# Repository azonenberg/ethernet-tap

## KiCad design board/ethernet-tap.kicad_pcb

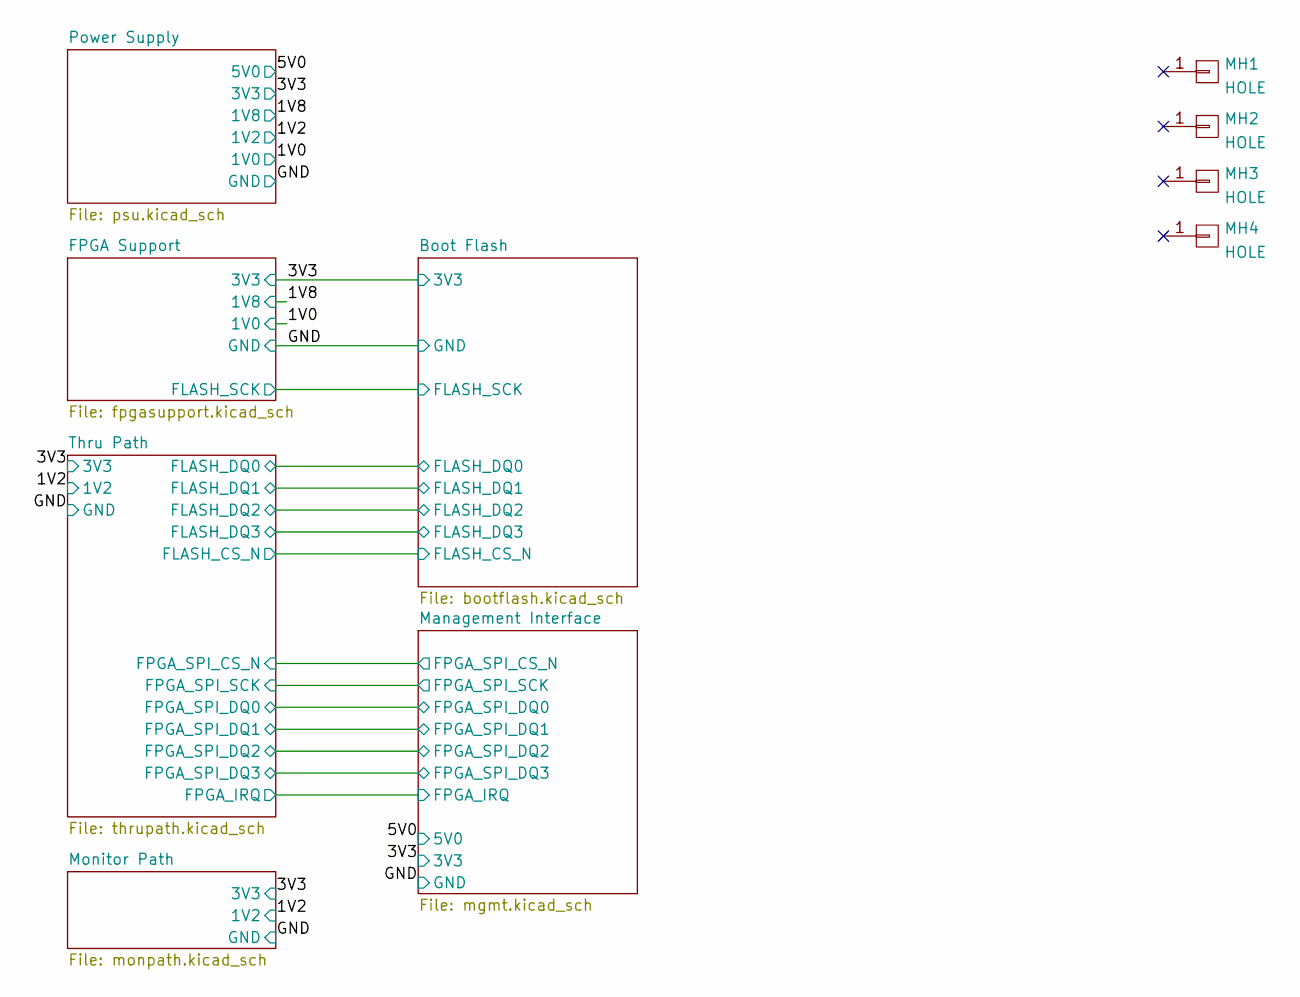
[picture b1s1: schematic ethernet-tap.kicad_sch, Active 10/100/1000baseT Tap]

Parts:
MH1, MH2, MH3, MH4: HOLE; MECHANICAL_CLEARANCEHOLE_4_40

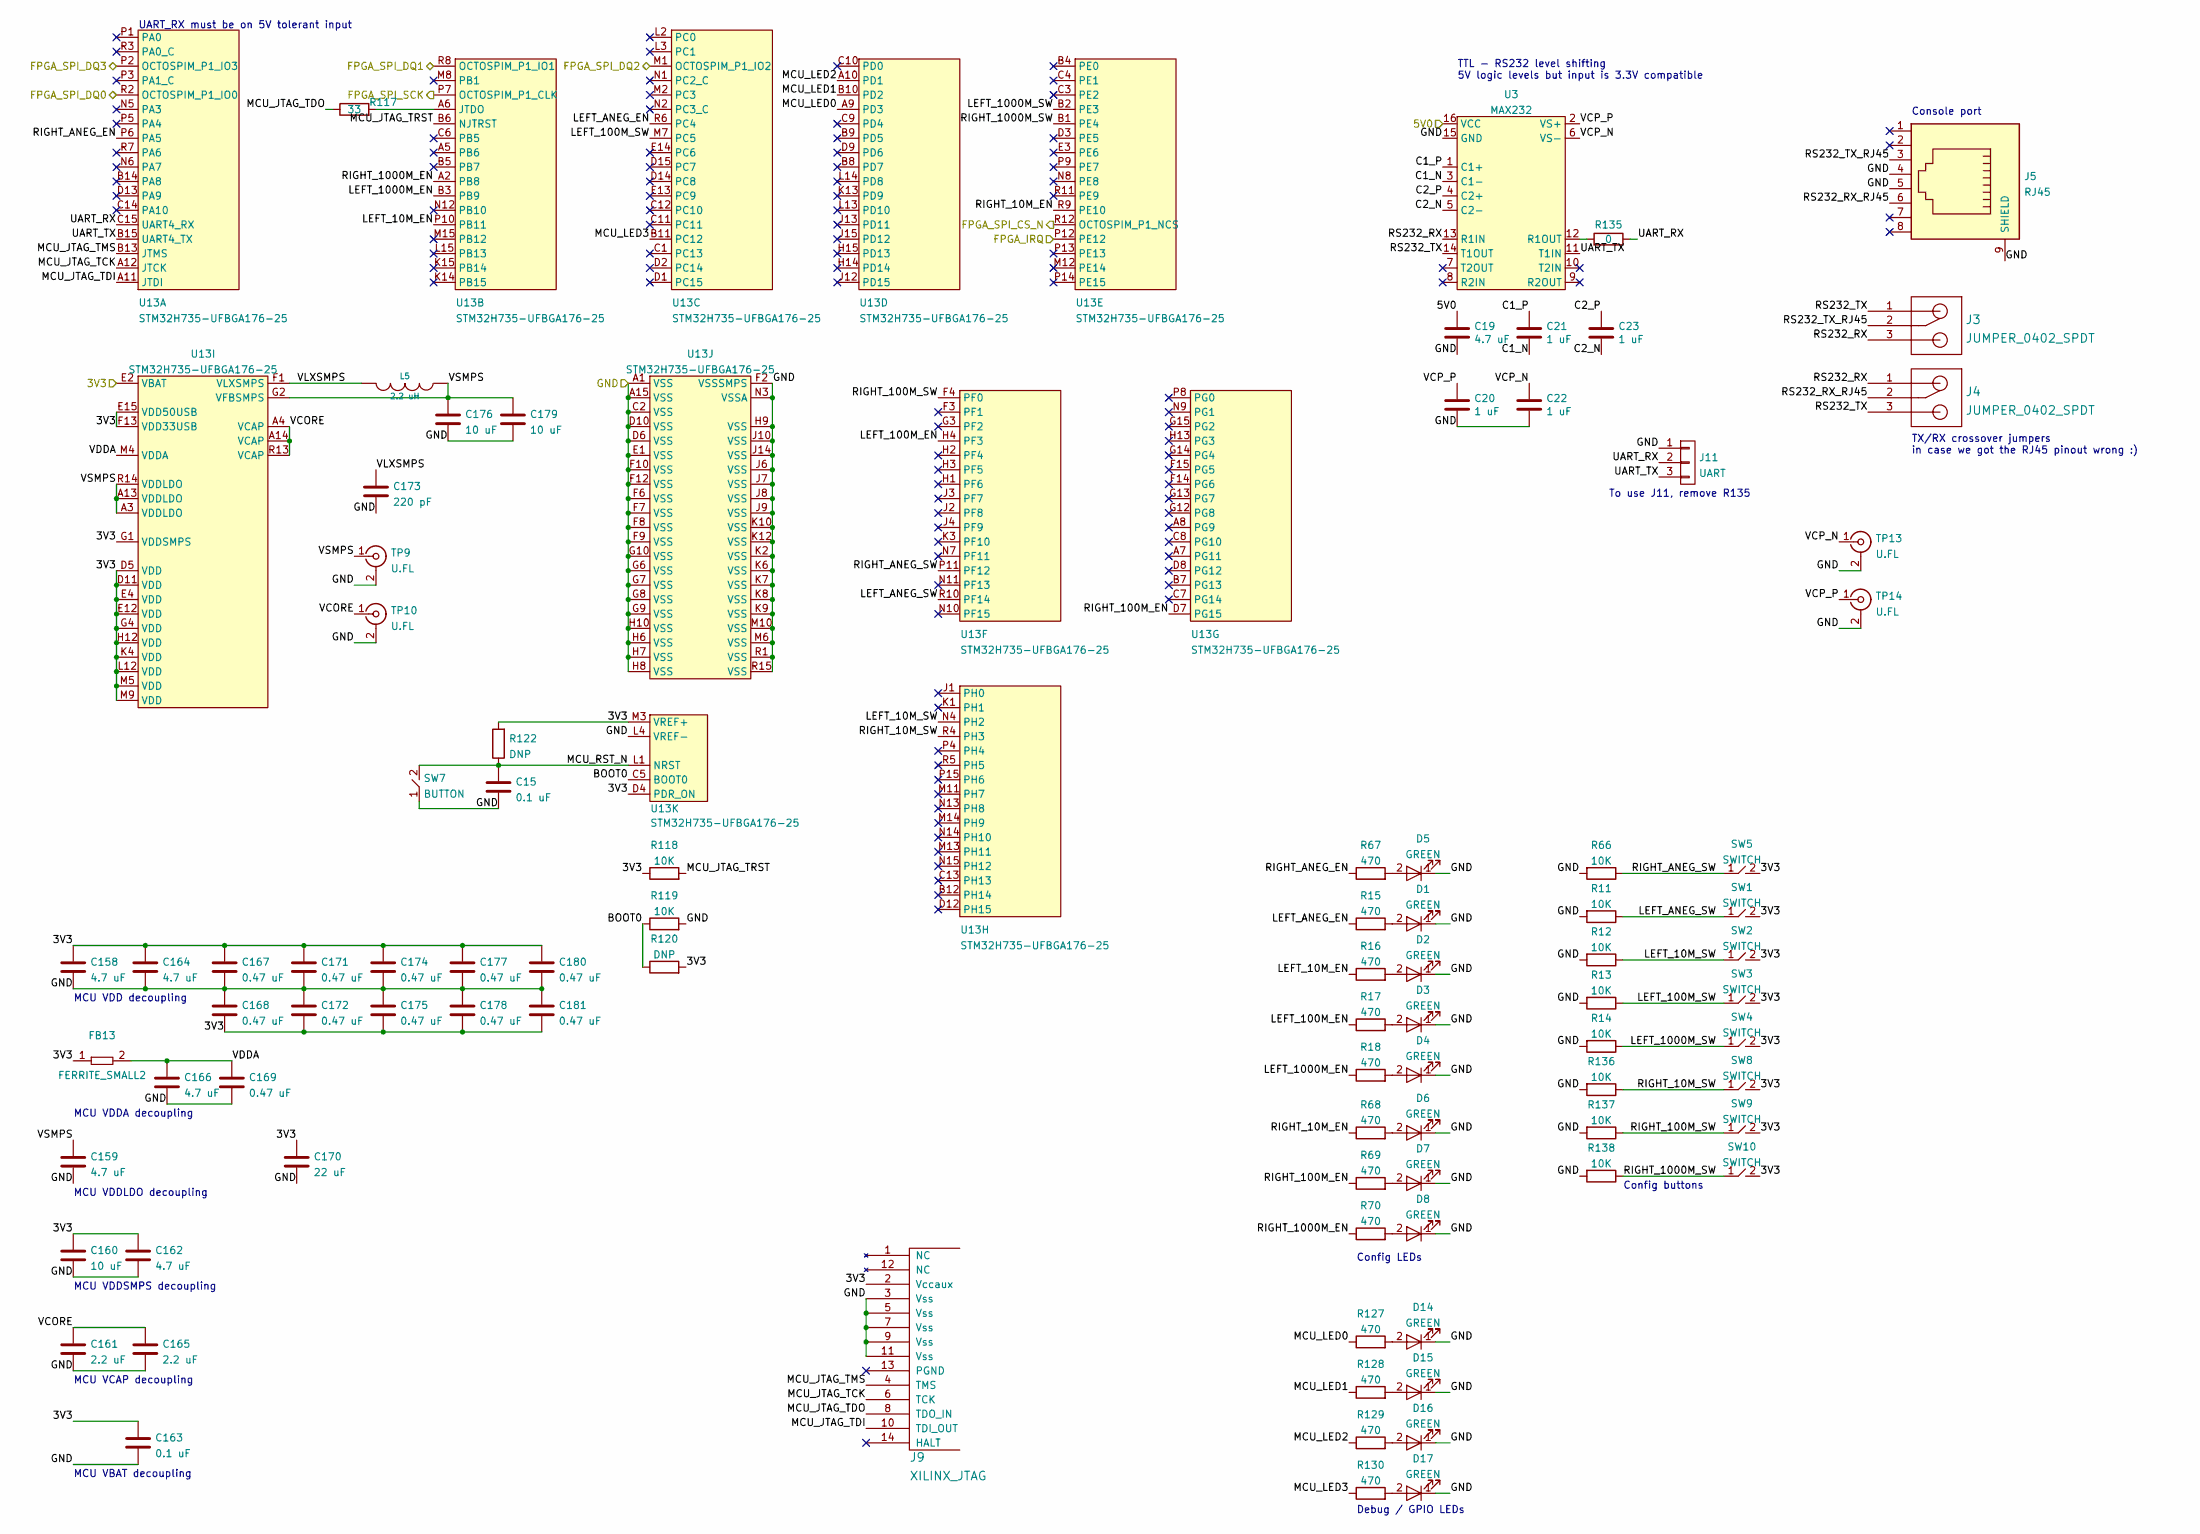
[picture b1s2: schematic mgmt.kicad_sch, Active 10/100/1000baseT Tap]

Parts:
C15, C163: 0.1 uF; EIA_0402_CAP_NOSILK
C19, C158, C159, C162, C164, C166: 4.7 uF; EIA_0603_CAP_NOSILK
C20, C21, C22, C23: 1 uF; EIA_0603_CAP_NOSILK
C160, C176, C179: 10 uF; EIA_0805_CAP_NOSILK
C161, C165: 2.2 uF; EIA_0603_CAP_NOSILK
C167, C168, C169, C171, C172, C174, C175, C177, C178, C180, C181: 0.47 uF; EIA_0402_CAP_NOSILK
C170: 22 uF; EIA_1206_CAP_NOSILK
C173: 220 pF; EIA_0402_CAP_NOSILK
D1, D2, D3, D4, D5, D6, D7, D8, D14, D15, D16, D17: GREEN; EIA_0603_LED
FB13: FERRITE_SMALL2; EIA_0603_INDUCTOR_NOSILK
J3, J4: JUMPER_0402_SPDT; EIA_0402_JUMPER
J5: RJ45; CONN_RJ45_BELSTEWART_SS-7188S-A-PG4-1-BA-xx
J9: XILINX_JTAG; XILINX_JTAG_PTH_MOLEX_0878311420
J11: UART; CONN_HEADER_2.54MM_1x3
L5: 2.2 uH; EIA_1210_CAP_NOSILK
R11, R12, R13, R14, R66, R118, R119, R136, R137, R138: 10K; EIA_0402_RES_NOSILK
R15, R16, R17, R18, R67, R68, R69, R70, R127, R128, R129, R130: 470; EIA_0402_RES_NOSILK
R117: 33; EIA_0402_RES_NOSILK
R120, R122: DNP; EIA_0402_RES_NOSILK
R135: 0; EIA_0402_RES_NOSILK
SW1, SW2, SW3, SW4, SW5, SW8, SW9, SW10: SWITCH; SWITCH_RAFI_MICON_5
SW7: BUTTON; SWITCH_RAFI_MICON_5
TP9, TP10, TP13, TP14: U.FL; CONN_U.FL_TE_1909763-1
U3: MAX232; SOIC_16_3.9MM
U13: STM32H735-UFBGA176-25; BGA_201_10x10_DEPOP_0.65MM_OSHPARK

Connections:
/3V3: C158.1, C160.1, C162.1, C163.1, C164.1, C167.1, C168.2, C170.1, C171.1, C172.2, C174.1, C175.2, C177.1, C178.2, C180.1, C181.2, FB13.1, J9.2 (Vccaux), R118.1, R120.2, R122.2, SW1.2, SW2.2, SW3.2, SW4.2, SW5.2, SW8.2, SW9.2, SW10.2, U13.D4 (PDR_ON), U13.D5 (VDD), U13.D11 (VDD), U13.E2 (VBAT), U13.E4 (VDD), U13.E12 (VDD), U13.E15 (VDD50USB), U13.F13 (VDD33USB), U13.G1 (VDDSMPS), U13.G4 (VDD), U13.H12 (VDD), U13.K4 (VDD), U13.L12 (VDD), U13.M3 (VREF+), U13.M5 (VDD), U13.M9 (VDD); also elsewhere on the board
/5V0: C19.1, U3.16 (VCC); also elsewhere on the board
/GND: C15.2, C19.2, C20.2, C22.2, C158.2, C159.2, C160.2, C161.2, C162.2, C163.2, C164.2, C165.2, C166.2, C167.2, C168.1, C169.2, C170.2, C171.2, C172.1, C173.2, C174.2, C175.1, C176.2, C177.2, C178.1, C179.2, C180.2, C181.1, D1.1 (K), D2.1 (K), D3.1 (K), D4.1 (K), D5.1 (K), D6.1 (K), D7.1 (K), D8.1 (K), D14.1 (K), D15.1 (K), D16.1 (K), D17.1 (K), J5.4, J5.5, J5.9 (SHIELD), J9.3 (Vss), J9.5 (Vss), J9.7 (Vss), J9.9 (Vss), J9.11 (Vss), J11.1, R11.2, R12.2, R13.2, R14.2, R66.2, R119.2, R136.2, R137.2, R138.2, SW7.1, TP9.2 (Ext), TP10.2 (Ext), TP13.2 (Ext), TP14.2 (Ext), U3.15 (GND), U13.A1 (VSS), U13.A15 (VSS), U13.C2 (VSS), U13.D6 (VSS), U13.D10 (VSS), U13.E1 (VSS), U13.F2 (VSSSMPS), U13.F6 (VSS), U13.F7 (VSS), U13.F8 (VSS), U13.F9 (VSS), U13.F10 (VSS), U13.F12 (VSS), U13.G6 (VSS), U13.G7 (VSS), U13.G8 (VSS), U13.G9 (VSS), U13.G10 (VSS), U13.H6 (VSS), U13.H7 (VSS), U13.H8 (VSS), U13.H9 (VSS), U13.H10 (VSS), U13.J6 (VSS), U13.J7 (VSS), U13.J8 (VSS), U13.J9 (VSS), U13.J10 (VSS), U13.J14 (VSS), U13.K2 (VSS), U13.K6 (VSS), U13.K7 (VSS), U13.K8 (VSS), U13.K9 (VSS), U13.K10 (VSS), U13.K12 (VSS), U13.L4 (VREF-), U13.M6 (VSS), U13.M10 (VSS), U13.N3 (VSSA), U13.R1 (VSS), U13.R15 (VSS); also elsewhere on the board
/Management Interface/BOOT0: R119.1, R120.1, U13.C5 (BOOT0)
/Management Interface/C1_N: C21.2, U3.3 (C1-)
/Management Interface/C1_P: C21.1, U3.1 (C1+)
/Management Interface/C2_N: C23.2, U3.5 (C2-)
/Management Interface/C2_P: C23.1, U3.4 (C2+)
/Management Interface/FPGA_IRQ: U13.P12 (PE12); also elsewhere on the board
/Management Interface/FPGA_SPI_CS_N: U13.R12 (OCTOSPIM_P1_NCS); also elsewhere on the board
/Management Interface/FPGA_SPI_DQ0: U13.R2 (OCTOSPIM_P1_IO0); also elsewhere on the board
/Management Interface/FPGA_SPI_DQ1: U13.R8 (OCTOSPIM_P1_IO1); also elsewhere on the board
/Management Interface/FPGA_SPI_DQ2: U13.M1 (OCTOSPIM_P1_IO2); also elsewhere on the board
/Management Interface/FPGA_SPI_DQ3: U13.P2 (OCTOSPIM_P1_IO3); also elsewhere on the board
/Management Interface/FPGA_SPI_SCK: U13.P7 (OCTOSPIM_P1_CLK); also elsewhere on the board
/Management Interface/LEFT_10M_EN: R16.1, U13.P10 (PB11)
/Management Interface/LEFT_10M_SW: R12.1, SW2.1, U13.N4 (PH2)
/Management Interface/LEFT_100M_EN: R17.1, U13.H4 (PF3)
/Management Interface/LEFT_100M_SW: R13.1, SW3.1, U13.M7 (PC5)
/Management Interface/LEFT_1000M_EN: R18.1, U13.B3 (PB9)
/Management Interface/LEFT_1000M_SW: R14.1, SW4.1, U13.B2 (PE3)
/Management Interface/LEFT_ANEG_EN: R15.1, U13.R6 (PC4)
/Management Interface/LEFT_ANEG_SW: R11.1, SW1.1, U13.R10 (PF14)
/Management Interface/MCU_JTAG_TCK: J9.6 (TCK), U13.A12 (JTCK)
/Management Interface/MCU_JTAG_TDI: J9.10 (TDI_OUT), U13.A11 (JTDI)
/Management Interface/MCU_JTAG_TDO: J9.8 (TDO_IN), R117.1
/Management Interface/MCU_JTAG_TMS: J9.4 (TMS), U13.B13 (JTMS)
/Management Interface/MCU_JTAG_TRST: R118.2, U13.B6 (NJTRST)
/Management Interface/MCU_LED0: R127.1, U13.A9 (PD3)
/Management Interface/MCU_LED1: R128.1, U13.B10 (PD2)
/Management Interface/MCU_LED2: R129.1, U13.A10 (PD1)
/Management Interface/MCU_LED3: R130.1, U13.B11 (PC12)
/Management Interface/MCU_RST_N: C15.1, R122.1, SW7.2, U13.L1 (NRST)
/Management Interface/RIGHT_10M_EN: R68.1, U13.R9 (PE10)
/Management Interface/RIGHT_10M_SW: R136.1, SW8.1, U13.R4 (PH3)
/Management Interface/RIGHT_100M_EN: R69.1, U13.D7 (PG15)
/Management Interface/RIGHT_100M_SW: R137.1, SW9.1, U13.F4 (PF0)
/Management Interface/RIGHT_1000M_EN: R70.1, U13.A2 (PB8)
/Management Interface/RIGHT_1000M_SW: R138.1, SW10.1, U13.B1 (PE4)
/Management Interface/RIGHT_ANEG_EN: R67.1, U13.P6 (PA5)
/Management Interface/RIGHT_ANEG_SW: R66.1, SW5.1, U13.P11 (PF12)
/Management Interface/RS232_RX: J3.3, J4.1, U3.13 (R1IN)
/Management Interface/RS232_RX_RJ45: J4.2, J5.6
/Management Interface/RS232_TX: J3.1, J4.3, U3.14 (T1OUT)
/Management Interface/RS232_TX_RJ45: J3.2, J5.3
/Management Interface/UART_RX: J11.2, R135.2, U13.C15 (UART4_RX)
/Management Interface/UART_TX: J11.3, U3.11 (T1IN), U13.B15 (UART4_TX)
/Management Interface/VCORE: C161.1, C165.1, TP10.1 (In), U13.A4 (VCAP), U13.A14 (VCAP), U13.R13 (VCAP)
/Management Interface/VCP_N: C22.1, TP13.1 (In), U3.6 (VS-)
/Management Interface/VCP_P: C20.1, TP14.1 (In), U3.2 (VS+)
/Management Interface/VDDA: C166.1, C169.1, FB13.2, U13.M4 (VDDA)
/Management Interface/VLXSMPS: C173.1, L5.2, U13.F1 (VLXSMPS)
/Management Interface/VSMPS: C159.1, C176.1, C179.1, L5.1, TP9.1 (In), U13.A3 (VDDLDO), U13.A13 (VDDLDO), U13.G2 (VFBSMPS), U13.R14 (VDDLDO)
unnamed: D1.2 (A), R15.2
unnamed: D2.2 (A), R16.2
unnamed: D3.2 (A), R17.2
unnamed: D4.2 (A), R18.2
unnamed: D5.2 (A), R67.2
unnamed: D6.2 (A), R68.2
unnamed: D7.2 (A), R69.2
unnamed: D8.2 (A), R70.2
unnamed: D14.2 (A), R127.2
unnamed: D15.2 (A), R128.2
unnamed: D16.2 (A), R129.2
unnamed: D17.2 (A), R130.2
unnamed: R117.2, U13.A6 (JTDO)
unnamed: R135.1, U3.12 (R1OUT)

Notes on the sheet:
TX/RX crossover jumpers in case we got the RJ45 pinout wrong :)
MCU VCAP decoupling
Config buttons
Console port
UART_RX must be on 5V tolerant input
To use J11, remove R135
MCU VDDSMPS decoupling
MCU VDDA decoupling
MCU VBAT decoupling
MCU VDD decoupling
Debug / GPIO LEDs
Config LEDs
MCU VDDLDO decoupling
TTL - RS232 level shifting 5V logic levels but input is 3.3V compatible

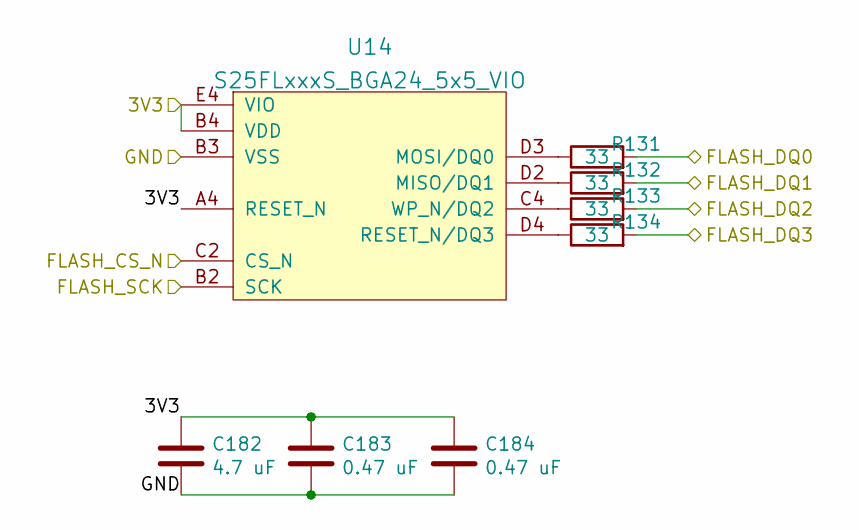
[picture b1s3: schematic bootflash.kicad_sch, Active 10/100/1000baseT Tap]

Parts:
C182: 4.7 uF; EIA_0603_CAP_NOSILK
C183, C184: 0.47 uF; EIA_0402_CAP_NOSILK
R131, R132, R133, R134: 33; EIA_0402_RES_NOSILK
U14: S25FLxxxS_BGA24_5x5_VIO; BGA_24_6x8_DEPOP1_1MM

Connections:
/3V3: C182.1, C183.1, C184.1, U14.A4 (RESET_N), U14.B4 (VDD), U14.E4 (VIO); also elsewhere on the board
/Boot Flash/FLASH_CS_N: U14.C2 (CS_N); also elsewhere on the board
/Boot Flash/FLASH_DQ0: R131.2; also elsewhere on the board
/Boot Flash/FLASH_DQ1: R132.2; also elsewhere on the board
/Boot Flash/FLASH_DQ2: R133.2; also elsewhere on the board
/Boot Flash/FLASH_DQ3: R134.2; also elsewhere on the board
/Boot Flash/FLASH_SCK: U14.B2 (SCK); also elsewhere on the board
/GND: C182.2, C183.2, C184.2, U14.B3 (VSS); also elsewhere on the board
unnamed: R131.1, U14.D3 (MOSI/DQ0)
unnamed: R132.1, U14.D2 (MISO/DQ1)
unnamed: R133.1, U14.C4 (WP_N/DQ2)
unnamed: R134.1, U14.D4 (RESET_N/DQ3)

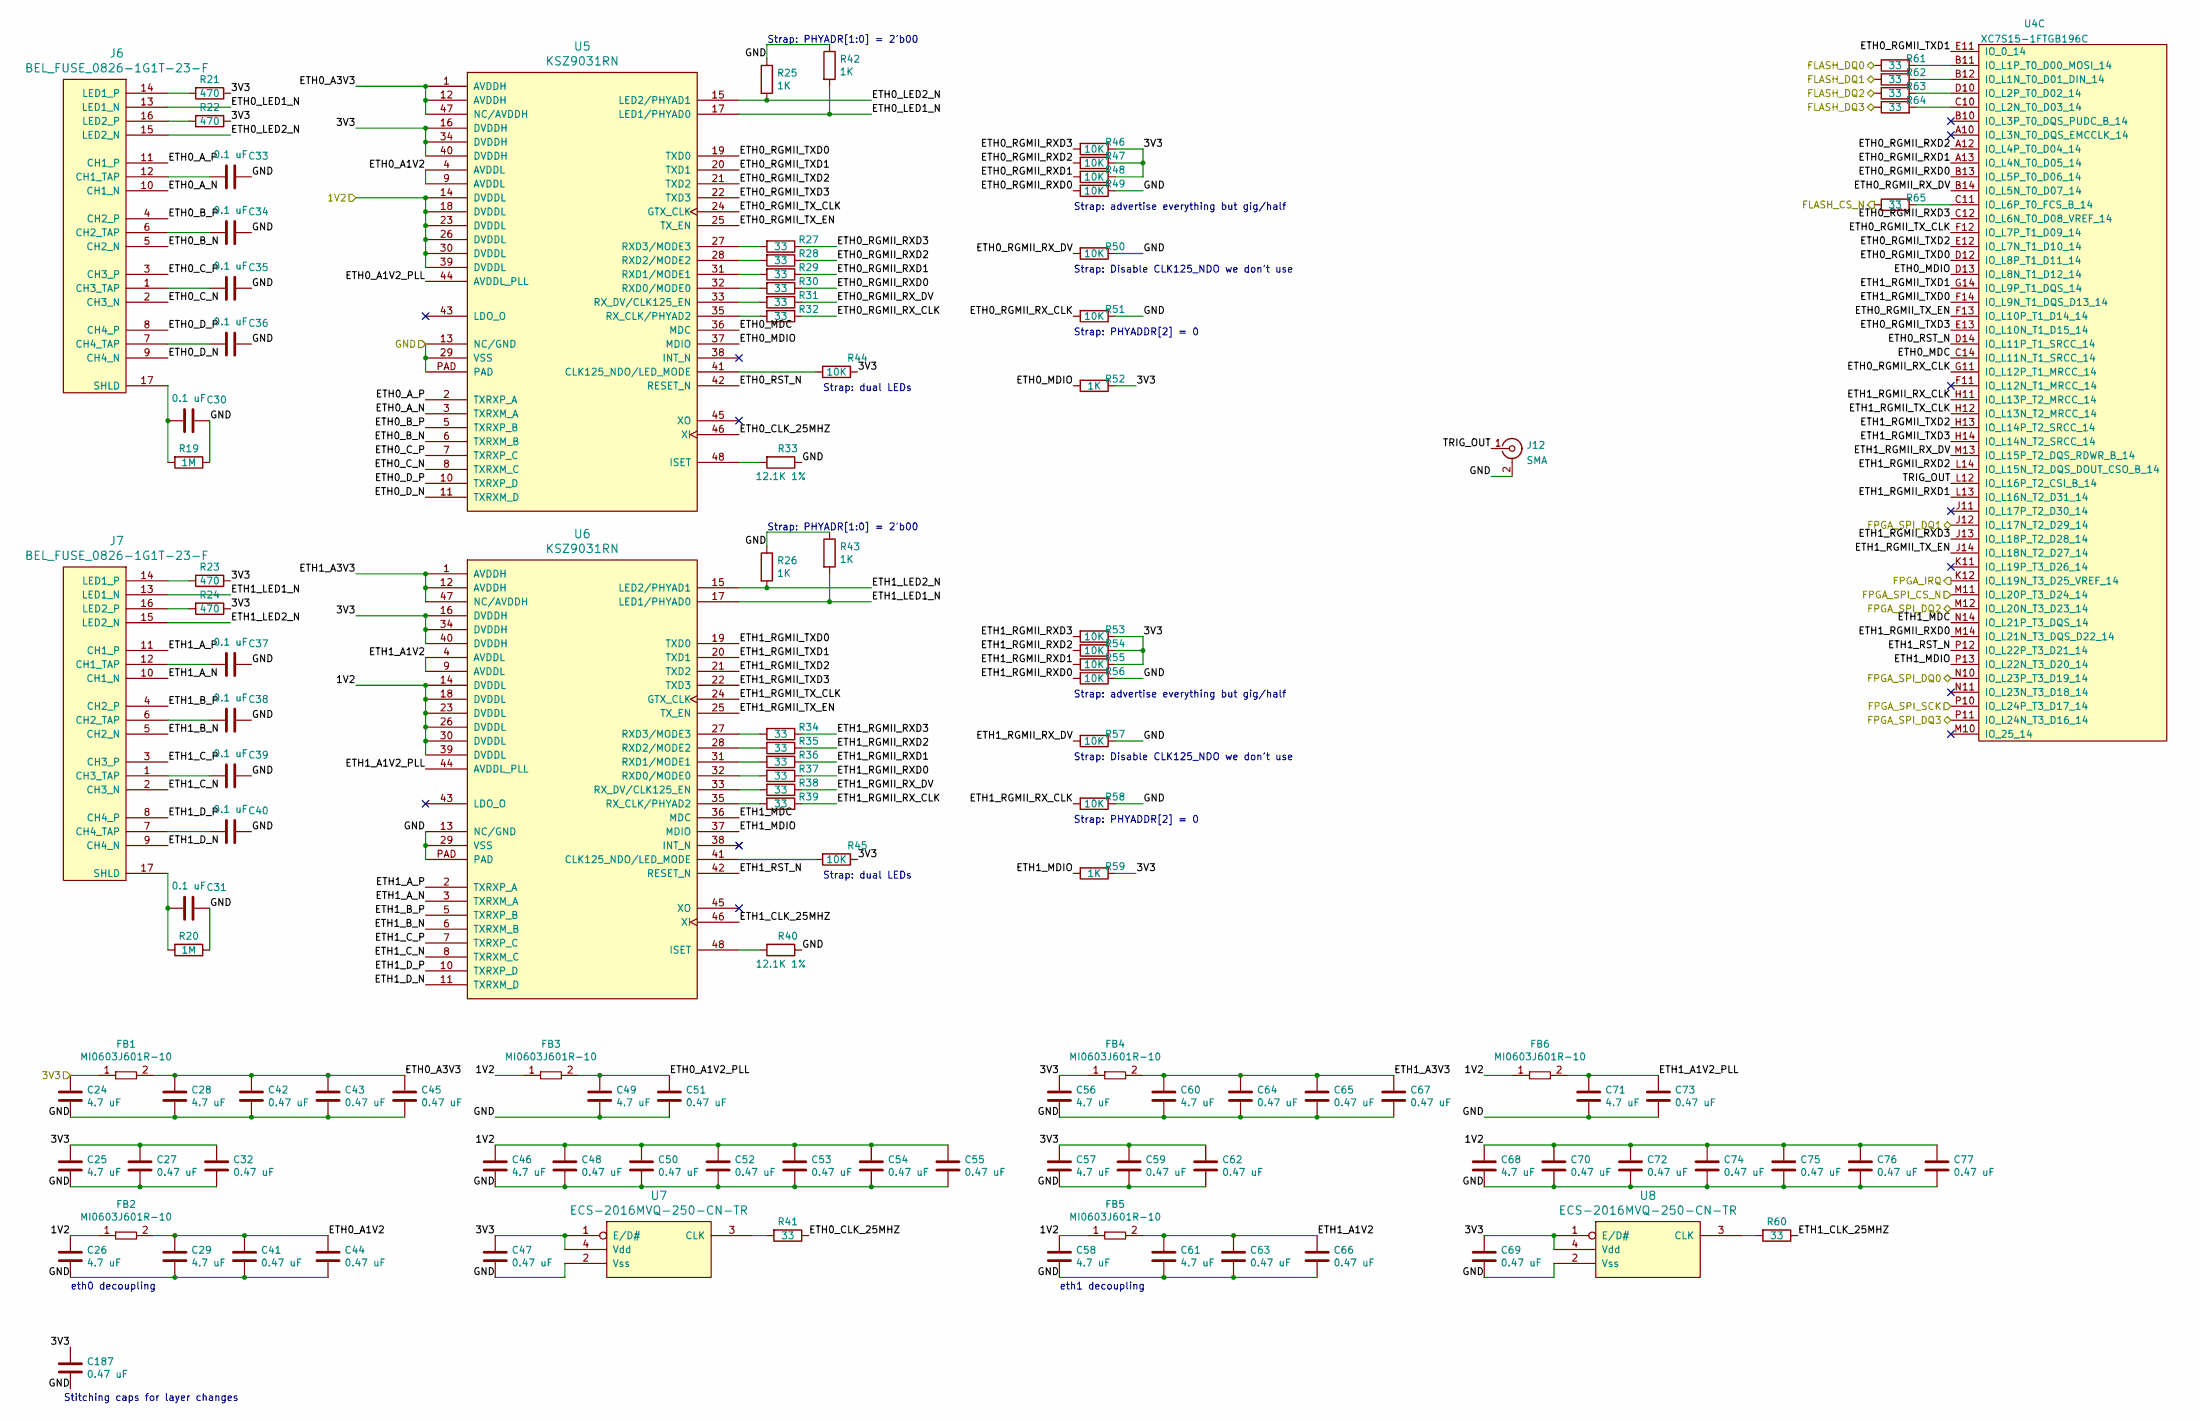
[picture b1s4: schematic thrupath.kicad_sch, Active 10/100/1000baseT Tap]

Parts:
C24, C25, C26, C28, C29, C46, C49, C56, C57, C58, C60, C61, C68, C71: 4.7 uF; EIA_0603_CAP_NOSILK
C27, C32, C41, C42, C43, C44, C45, C47, C48, C50, C51, C52, C53, C54, C55, C59, C62, C63, C64, C65, C66, C67, C69, C70, C72, C73, C74, C75, C76, C77, C187: 0.47 uF; EIA_0402_CAP_NOSILK
C30, C31, C33, C34, C35, C36, C37, C38, C39, C40: 0.1 uF; EIA_0402_CAP_NOSILK
FB1, FB2, FB3, FB4, FB5, FB6: MI0603J601R-10; EIA_0603_INDUCTOR_NOSILK
J6, J7: BEL_FUSE_0826-1G1T-23-F; CONN_BELFUSE_0826_1G1T_23_F
J12: SMA; CONN_SMA_EDGE_SAMTEC_SMA_J_P_H_ST_EM1
R19, R20: 1M; EIA_0402_RES_NOSILK
R21, R22, R23, R24: 470; EIA_0402_RES_NOSILK
R25, R26, R42, R43, R52, R59: 1K; EIA_0402_RES_NOSILK
R27, R28, R29, R30, R31, R32, R34, R35, R36, R37, R38, R39, R41, R60, R61, R62, R63, R64, R65: 33; EIA_0402_RES_NOSILK
R33, R40: 12.1K 1%; EIA_0402_RES_NOSILK
R44, R45, R46, R47, R48, R49, R50, R51, R53, R54, R55, R56, R57, R58: 10K; EIA_0402_RES_NOSILK
U4: XC7S15-1FTGB196C; BGA_196_15x15_FULLARRAY_1MM_FTGB196
U5, U6: KSZ9031RN; QFN_48_0.5MM_7x7MM
U7, U8: ECS-2016MVQ-250-CN-TR; OSCILLATOR_2.0x1.6

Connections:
/1V2: C26.1, C46.1, C48.1, C50.1, C52.1, C53.1, C54.1, C55.1, C58.1, C68.1, C70.1, C72.1, C74.1, C75.1, C76.1, C77.1, FB2.1, FB3.1, FB5.1, FB6.1, U5.14 (DVDDL), U5.18 (DVDDL), U5.23 (DVDDL), U5.26 (DVDDL), U5.30 (DVDDL), U5.39 (DVDDL), U6.14 (DVDDL), U6.18 (DVDDL), U6.23 (DVDDL), U6.26 (DVDDL), U6.30 (DVDDL), U6.39 (DVDDL); also elsewhere on the board
/3V3: C24.1, C25.1, C27.1, C32.1, C47.1, C56.1, C57.1, C59.1, C62.1, C69.1, C187.1, FB1.1, FB4.1, R21.1, R22.1, R23.1, R24.1, R44.1, R45.1, R46.1, R47.1, R48.1, R52.1, R53.1, R54.1, R55.1, R59.1, U5.16 (DVDDH), U5.34 (DVDDH), U5.40 (DVDDH), U6.16 (DVDDH), U6.34 (DVDDH), U6.40 (DVDDH), U7.1 (E/D#), U7.4 (Vdd), U8.1 (E/D#), U8.4 (Vdd); also elsewhere on the board
/Boot Flash/FLASH_CS_N: R65.1; also elsewhere on the board
/Boot Flash/FLASH_DQ0: R61.1; also elsewhere on the board
/Boot Flash/FLASH_DQ1: R62.1; also elsewhere on the board
/Boot Flash/FLASH_DQ2: R63.1; also elsewhere on the board
/Boot Flash/FLASH_DQ3: R64.1; also elsewhere on the board
/GND: C24.2, C25.2, C26.2, C27.2, C28.2, C29.2, C30.1, C31.1, C32.2, C33.1, C34.1, C35.1, C36.1, C37.1, C38.1, C39.1, C40.1, C41.2, C42.2, C43.2, C44.2, C45.2, C46.2, C47.2, C48.2, C49.2, C50.2, C51.2, C52.2, C53.2, C54.2, C55.2, C56.2, C57.2, C58.2, C59.2, C60.2, C61.2, C62.2, C63.2, C64.2, C65.2, C66.2, C67.2, C68.2, C69.2, C70.2, C71.2, C72.2, C73.2, C74.2, C75.2, C76.2, C77.2, C187.2, J12.2 (Ext), R19.1, R20.1, R25.1, R26.1, R33.1, R40.1, R42.1, R43.1, R49.1, R50.1, R51.1, R56.1, R57.1, R58.1, U5.13 (NC/GND), U5.29 (VSS), U5.PAD, U6.13 (NC/GND), U6.29 (VSS), U6.PAD, U7.2 (Vss), U8.2 (Vss); also elsewhere on the board
/Management Interface/FPGA_IRQ: U4.K12 (IO_L19N_T3_D25_VREF_14); also elsewhere on the board
/Management Interface/FPGA_SPI_CS_N: U4.M11 (IO_L20P_T3_D24_14); also elsewhere on the board
/Management Interface/FPGA_SPI_DQ0: U4.N10 (IO_L23P_T3_D19_14); also elsewhere on the board
/Management Interface/FPGA_SPI_DQ1: U4.J12 (IO_L17N_T2_D29_14); also elsewhere on the board
/Management Interface/FPGA_SPI_DQ2: U4.M12 (IO_L20N_T3_D23_14); also elsewhere on the board
/Management Interface/FPGA_SPI_DQ3: U4.P11 (IO_L24N_T3_D16_14); also elsewhere on the board
/Management Interface/FPGA_SPI_SCK: U4.P10 (IO_L24P_T3_D17_14); also elsewhere on the board
/Thru Path/ETH0_A1V2: C29.1, C41.1, C44.1, FB2.2, U5.4 (AVDDL), U5.9 (AVDDL)
/Thru Path/ETH0_A1V2_PLL: C49.1, C51.1, FB3.2, U5.44 (AVDDL_PLL)
/Thru Path/ETH0_A3V3: C28.1, C42.1, C43.1, C45.1, FB1.2, U5.1 (AVDDH), U5.12 (AVDDH), U5.47 (NC/AVDDH)
/Thru Path/ETH0_A_N: J6.10 (CH1_N), U5.3 (TXRXM_A)
/Thru Path/ETH0_A_P: J6.11 (CH1_P), U5.2 (TXRXP_A)
/Thru Path/ETH0_B_N: J6.5 (CH2_N), U5.6 (TXRXM_B)
/Thru Path/ETH0_B_P: J6.4 (CH2_P), U5.5 (TXRXP_B)
/Thru Path/ETH0_CLK_25MHZ: R41.1, U5.46 (XI)
/Thru Path/ETH0_C_N: J6.2 (CH3_N), U5.8 (TXRXM_C)
/Thru Path/ETH0_C_P: J6.3 (CH3_P), U5.7 (TXRXP_C)
/Thru Path/ETH0_D_N: J6.9 (CH4_N), U5.11 (TXRXM_D)
/Thru Path/ETH0_D_P: J6.8 (CH4_P), U5.10 (TXRXP_D)
/Thru Path/ETH0_LED1_N: J6.13 (LED1_N), R42.2, U5.17 (LED1/PHYAD0)
/Thru Path/ETH0_LED2_N: J6.15 (LED2_N), R25.2, U5.15 (LED2/PHYAD1)
/Thru Path/ETH0_MDC: U4.C14 (IO_L11N_T1_SRCC_14), U5.36 (MDC)
/Thru Path/ETH0_MDIO: R52.2, U4.D13 (IO_L8N_T1_D12_14), U5.37 (MDIO)
/Thru Path/ETH0_RGMII_RXD0: R30.1, R49.2, U4.B13 (IO_L5P_T0_D06_14)
/Thru Path/ETH0_RGMII_RXD1: R29.1, R48.2, U4.A13 (IO_L4N_T0_D05_14)
/Thru Path/ETH0_RGMII_RXD2: R28.1, R47.2, U4.A12 (IO_L4P_T0_D04_14)
/Thru Path/ETH0_RGMII_RXD3: R27.1, R46.2, U4.C12 (IO_L6N_T0_D08_VREF_14)
/Thru Path/ETH0_RGMII_RX_CLK: R32.1, R51.2, U4.G11 (IO_L12P_T1_MRCC_14)
/Thru Path/ETH0_RGMII_RX_DV: R31.1, R50.2, U4.B14 (IO_L5N_T0_D07_14)
/Thru Path/ETH0_RGMII_TXD0: U4.D12 (IO_L8P_T1_D11_14), U5.19 (TXD0)
/Thru Path/ETH0_RGMII_TXD1: U4.E11 (IO_0_14), U5.20 (TXD1)
/Thru Path/ETH0_RGMII_TXD2: U4.E12 (IO_L7N_T1_D10_14), U5.21 (TXD2)
/Thru Path/ETH0_RGMII_TXD3: U4.E13 (IO_L10N_T1_D15_14), U5.22 (TXD3)
/Thru Path/ETH0_RGMII_TX_CLK: U4.F12 (IO_L7P_T1_D09_14), U5.24 (GTX_CLK)
/Thru Path/ETH0_RGMII_TX_EN: U4.F13 (IO_L10P_T1_D14_14), U5.25 (TX_EN)
/Thru Path/ETH0_RST_N: U4.D14 (IO_L11P_T1_SRCC_14), U5.42 (RESET_N)
/Thru Path/ETH1_A1V2: C61.1, C63.1, C66.1, FB5.2, U6.4 (AVDDL), U6.9 (AVDDL)
/Thru Path/ETH1_A1V2_PLL: C71.1, C73.1, FB6.2, U6.44 (AVDDL_PLL)
/Thru Path/ETH1_A3V3: C60.1, C64.1, C65.1, C67.1, FB4.2, U6.1 (AVDDH), U6.12 (AVDDH), U6.47 (NC/AVDDH)
/Thru Path/ETH1_A_N: J7.10 (CH1_N), U6.3 (TXRXM_A)
/Thru Path/ETH1_A_P: J7.11 (CH1_P), U6.2 (TXRXP_A)
/Thru Path/ETH1_B_N: J7.5 (CH2_N), U6.6 (TXRXM_B)
/Thru Path/ETH1_B_P: J7.4 (CH2_P), U6.5 (TXRXP_B)
/Thru Path/ETH1_CLK_25MHZ: R60.1, U6.46 (XI)
/Thru Path/ETH1_C_N: J7.2 (CH3_N), U6.8 (TXRXM_C)
/Thru Path/ETH1_C_P: J7.3 (CH3_P), U6.7 (TXRXP_C)
/Thru Path/ETH1_D_N: J7.9 (CH4_N), U6.11 (TXRXM_D)
/Thru Path/ETH1_D_P: J7.8 (CH4_P), U6.10 (TXRXP_D)
/Thru Path/ETH1_LED1_N: J7.13 (LED1_N), R43.2, U6.17 (LED1/PHYAD0)
/Thru Path/ETH1_LED2_N: J7.15 (LED2_N), R26.2, U6.15 (LED2/PHYAD1)
/Thru Path/ETH1_MDC: U4.N14 (IO_L21P_T3_DQS_14), U6.36 (MDC)
/Thru Path/ETH1_MDIO: R59.2, U4.P13 (IO_L22N_T3_D20_14), U6.37 (MDIO)
/Thru Path/ETH1_RGMII_RXD0: R37.1, R56.2, U4.M14 (IO_L21N_T3_DQS_D22_14)
/Thru Path/ETH1_RGMII_RXD1: R36.1, R55.2, U4.L13 (IO_L16N_T2_D31_14)
/Thru Path/ETH1_RGMII_RXD2: R35.1, R54.2, U4.L14 (IO_L15N_T2_DQS_DOUT_CSO_B_14)
/Thru Path/ETH1_RGMII_RXD3: R34.1, R53.2, U4.J13 (IO_L18P_T2_D28_14)
/Thru Path/ETH1_RGMII_RX_CLK: R39.1, R58.2, U4.H11 (IO_L13P_T2_MRCC_14)
/Thru Path/ETH1_RGMII_RX_DV: R38.1, R57.2, U4.M13 (IO_L15P_T2_DQS_RDWR_B_14)
/Thru Path/ETH1_RGMII_TXD0: U4.F14 (IO_L9N_T1_DQS_D13_14), U6.19 (TXD0)
/Thru Path/ETH1_RGMII_TXD1: U4.G14 (IO_L9P_T1_DQS_14), U6.20 (TXD1)
/Thru Path/ETH1_RGMII_TXD2: U4.H13 (IO_L14P_T2_SRCC_14), U6.21 (TXD2)
/Thru Path/ETH1_RGMII_TXD3: U4.H14 (IO_L14N_T2_SRCC_14), U6.22 (TXD3)
/Thru Path/ETH1_RGMII_TX_CLK: U4.H12 (IO_L13N_T2_MRCC_14), U6.24 (GTX_CLK)
/Thru Path/ETH1_RGMII_TX_EN: U4.J14 (IO_L18N_T2_D27_14), U6.25 (TX_EN)
/Thru Path/ETH1_RST_N: U4.P12 (IO_L22P_T3_D21_14), U6.42 (RESET_N)
/Thru Path/TRIG_OUT: J12.1 (In), U4.L12 (IO_L16P_T2_CSI_B_14)
unnamed: C30.2, J6.17 (SHLD), R19.2
unnamed: C31.2, J7.17 (SHLD), R20.2
unnamed: C33.2, J6.12 (CH1_TAP)
unnamed: C34.2, J6.6 (CH2_TAP)
unnamed: C35.2, J6.1 (CH3_TAP)
unnamed: C36.2, J6.7 (CH4_TAP)
unnamed: C37.2, J7.12 (CH1_TAP)
unnamed: C38.2, J7.6 (CH2_TAP)
unnamed: C39.2, J7.1 (CH3_TAP)
unnamed: C40.2, J7.7 (CH4_TAP)
unnamed: J6.14 (LED1_P), R21.2
unnamed: J6.16 (LED2_P), R22.2
unnamed: J7.14 (LED1_P), R23.2
unnamed: J7.16 (LED2_P), R24.2
unnamed: R27.2, U5.27 (RXD3/MODE3)
unnamed: R28.2, U5.28 (RXD2/MODE2)
unnamed: R29.2, U5.31 (RXD1/MODE1)
unnamed: R30.2, U5.32 (RXD0/MODE0)
unnamed: R31.2, U5.33 (RX_DV/CLK125_EN)
unnamed: R32.2, U5.35 (RX_CLK/PHYAD2)
unnamed: R33.2, U5.48 (ISET)
unnamed: R34.2, U6.27 (RXD3/MODE3)
unnamed: R35.2, U6.28 (RXD2/MODE2)
unnamed: R36.2, U6.31 (RXD1/MODE1)
unnamed: R37.2, U6.32 (RXD0/MODE0)
unnamed: R38.2, U6.33 (RX_DV/CLK125_EN)
unnamed: R39.2, U6.35 (RX_CLK/PHYAD2)
unnamed: R40.2, U6.48 (ISET)
unnamed: R41.2, U7.3 (CLK)
unnamed: R44.2, U5.41 (CLK125_NDO/LED_MODE)
unnamed: R45.2, U6.41 (CLK125_NDO/LED_MODE)
unnamed: R60.2, U8.3 (CLK)
unnamed: R61.2, U4.B11 (IO_L1P_T0_D00_MOSI_14)
unnamed: R62.2, U4.B12 (IO_L1N_T0_D01_DIN_14)
unnamed: R63.2, U4.D10 (IO_L2P_T0_D02_14)
unnamed: R64.2, U4.C10 (IO_L2N_T0_D03_14)
unnamed: R65.2, U4.C11 (IO_L6P_T0_FCS_B_14)

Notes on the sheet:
Strap: advertise everything but gig/half
Strap: dual LEDs
Stitching caps for layer changes
Strap: PHYADDR[2] = 0
eth1 decoupling
Strap: PHYADR[1:0] = 2'b00
Strap: Disable CLK125_NDO we don't use
eth0 decoupling

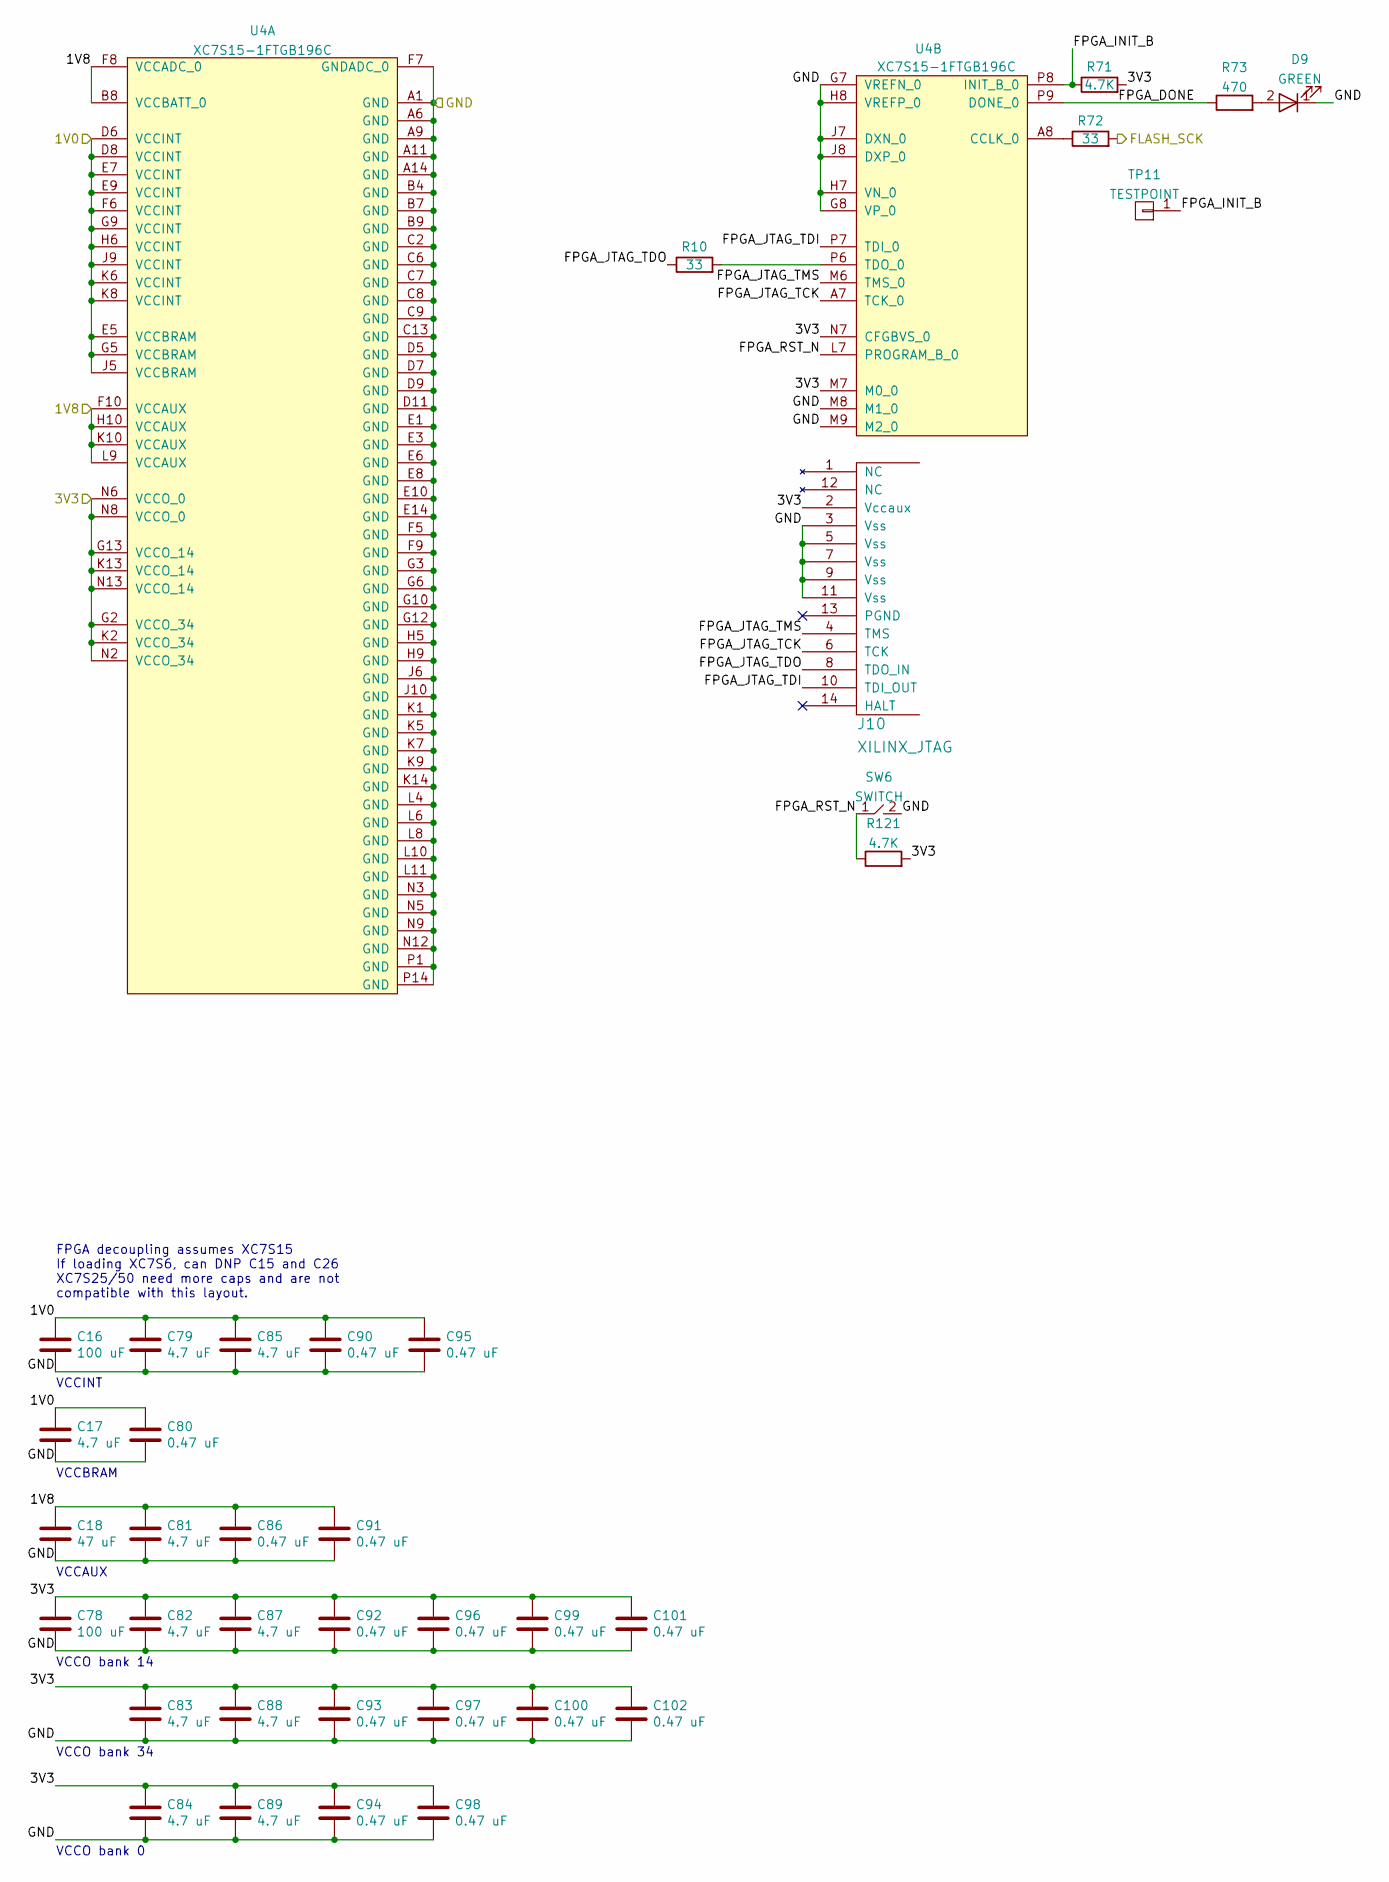
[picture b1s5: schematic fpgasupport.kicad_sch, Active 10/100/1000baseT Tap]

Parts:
C16: 100 uF; EIA_1210_CAP_NOSILK
C17, C79, C81, C82, C83, C84, C85, C87, C88, C89: 4.7 uF; EIA_0603_CAP_NOSILK
C18: 47 uF; EIA_1206_CAP_NOSILK
C78: 100 uF; EIA_1206_CAP_NOSILK
C80, C86, C90, C91, C92, C93, C94, C95, C96, C97, C98, C99, C100, C101, C102: 0.47 uF; EIA_0402_CAP_NOSILK
D9: GREEN; EIA_0603_LED
J10: XILINX_JTAG; XILINX_JTAG_PTH_MOLEX_0878311420
R10, R72: 33; EIA_0402_RES_NOSILK
R71, R121: 4.7K; EIA_0402_RES_NOSILK
R73: 470; EIA_0402_RES_NOSILK
SW6: SWITCH; SWITCH_RAFI_MICON_5
TP11: TESTPOINT; TESTPOINT_SMT_0.5MM
U4: XC7S15-1FTGB196C; BGA_196_15x15_FULLARRAY_1MM_FTGB196

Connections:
/1V0: C16.1, C17.1, C79.1, C80.1, C85.1, C90.1, C95.1, U4.D6 (VCCINT), U4.D8 (VCCINT), U4.E5 (VCCBRAM), U4.E7 (VCCINT), U4.E9 (VCCINT), U4.F6 (VCCINT), U4.G5 (VCCBRAM), U4.G9 (VCCINT), U4.H6 (VCCINT), U4.J5 (VCCBRAM), U4.J9 (VCCINT), U4.K6 (VCCINT), U4.K8 (VCCINT); also elsewhere on the board
/1V8: C18.1, C81.1, C86.1, C91.1, U4.B8 (VCCBATT_0), U4.F8 (VCCADC_0), U4.F10 (VCCAUX), U4.H10 (VCCAUX), U4.K10 (VCCAUX), U4.L9 (VCCAUX); also elsewhere on the board
/3V3: C78.1, C82.1, C83.1, C84.1, C87.1, C88.1, C89.1, C92.1, C93.1, C94.1, C96.1, C97.1, C98.1, C99.1, C100.1, C101.1, C102.1, J10.2 (Vccaux), R71.2, R121.2, U4.G2 (VCCO_34), U4.G13 (VCCO_14), U4.K2 (VCCO_34), U4.K13 (VCCO_14), U4.M7 (M0_0), U4.N2 (VCCO_34), U4.N6 (VCCO_0), U4.N7 (CFGBVS_0), U4.N8 (VCCO_0), U4.N13 (VCCO_14); also elsewhere on the board
/Boot Flash/FLASH_SCK: R72.2; also elsewhere on the board
/FPGA Support/FPGA_DONE: R73.1, U4.P9 (DONE_0)
/FPGA Support/FPGA_INIT_B: R71.1, TP11.1, U4.P8 (INIT_B_0)
/FPGA Support/FPGA_JTAG_TCK: J10.6 (TCK), U4.A7 (TCK_0)
/FPGA Support/FPGA_JTAG_TDI: J10.10 (TDI_OUT), U4.P7 (TDI_0)
/FPGA Support/FPGA_JTAG_TDO: J10.8 (TDO_IN), R10.1
/FPGA Support/FPGA_JTAG_TMS: J10.4 (TMS), U4.M6 (TMS_0)
/FPGA Support/FPGA_RST_N: R121.1, SW6.1, U4.L7 (PROGRAM_B_0)
/GND: C16.2, C17.2, C18.2, C78.2, C79.2, C80.2, C81.2, C82.2, C83.2, C84.2, C85.2, C86.2, C87.2, C88.2, C89.2, C90.2, C91.2, C92.2, C93.2, C94.2, C95.2, C96.2, C97.2, C98.2, C99.2, C100.2, C101.2, C102.2, D9.1 (K), J10.3 (Vss), J10.5 (Vss), J10.7 (Vss), J10.9 (Vss), J10.11 (Vss), SW6.2, U4.A1 (GND), U4.A6 (GND), U4.A9 (GND), U4.A11 (GND), U4.A14 (GND), U4.B4 (GND), U4.B7 (GND), U4.B9 (GND), U4.C2 (GND), U4.C6 (GND), U4.C7 (GND), U4.C8 (GND), U4.C9 (GND), U4.C13 (GND), U4.D5 (GND), U4.D7 (GND), U4.D9 (GND), U4.D11 (GND), U4.E1 (GND), U4.E3 (GND), U4.E6 (GND), U4.E8 (GND), U4.E10 (GND), U4.E14 (GND), U4.F5 (GND), U4.F7 (GNDADC_0), U4.F9 (GND), U4.G3 (GND), U4.G6 (GND), U4.G7 (VREFN_0), U4.G8 (VP_0), U4.G10 (GND), U4.G12 (GND), U4.H5 (GND), U4.H7 (VN_0), U4.H8 (VREFP_0), U4.H9 (GND), U4.J6 (GND), U4.J7 (DXN_0), U4.J8 (DXP_0), U4.J10 (GND), U4.K1 (GND), U4.K5 (GND), U4.K7 (GND), U4.K9 (GND), U4.K14 (GND), U4.L4 (GND), U4.L6 (GND), U4.L8 (GND), U4.L10 (GND), U4.L11 (GND), U4.M8 (M1_0), U4.M9 (M2_0), U4.N3 (GND), U4.N5 (GND), U4.N9 (GND), U4.N12 (GND), U4.P1 (GND), U4.P14 (GND); also elsewhere on the board
unnamed: D9.2 (A), R73.2
unnamed: R10.2, U4.P6 (TDO_0)
unnamed: R72.1, U4.A8 (CCLK_0)

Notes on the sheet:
VCCINT
VCCO bank 0
VCCO bank 34
VCCO bank 14
FPGA decoupling assumes XC7S15 If loading XC7S6, can DNP C15 and C26 XC7S25/50 need more caps and are not compatible with this layout.
VCCAUX
VCCBRAM

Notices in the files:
firmware/main.cpp:
Copyright (c) 2023 Andrew D. Zonenberg and contributors
All rights reserved.
